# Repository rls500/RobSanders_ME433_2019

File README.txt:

Rob Sanders
4/9/2019

This is my repository for ME433 2019

This is a change

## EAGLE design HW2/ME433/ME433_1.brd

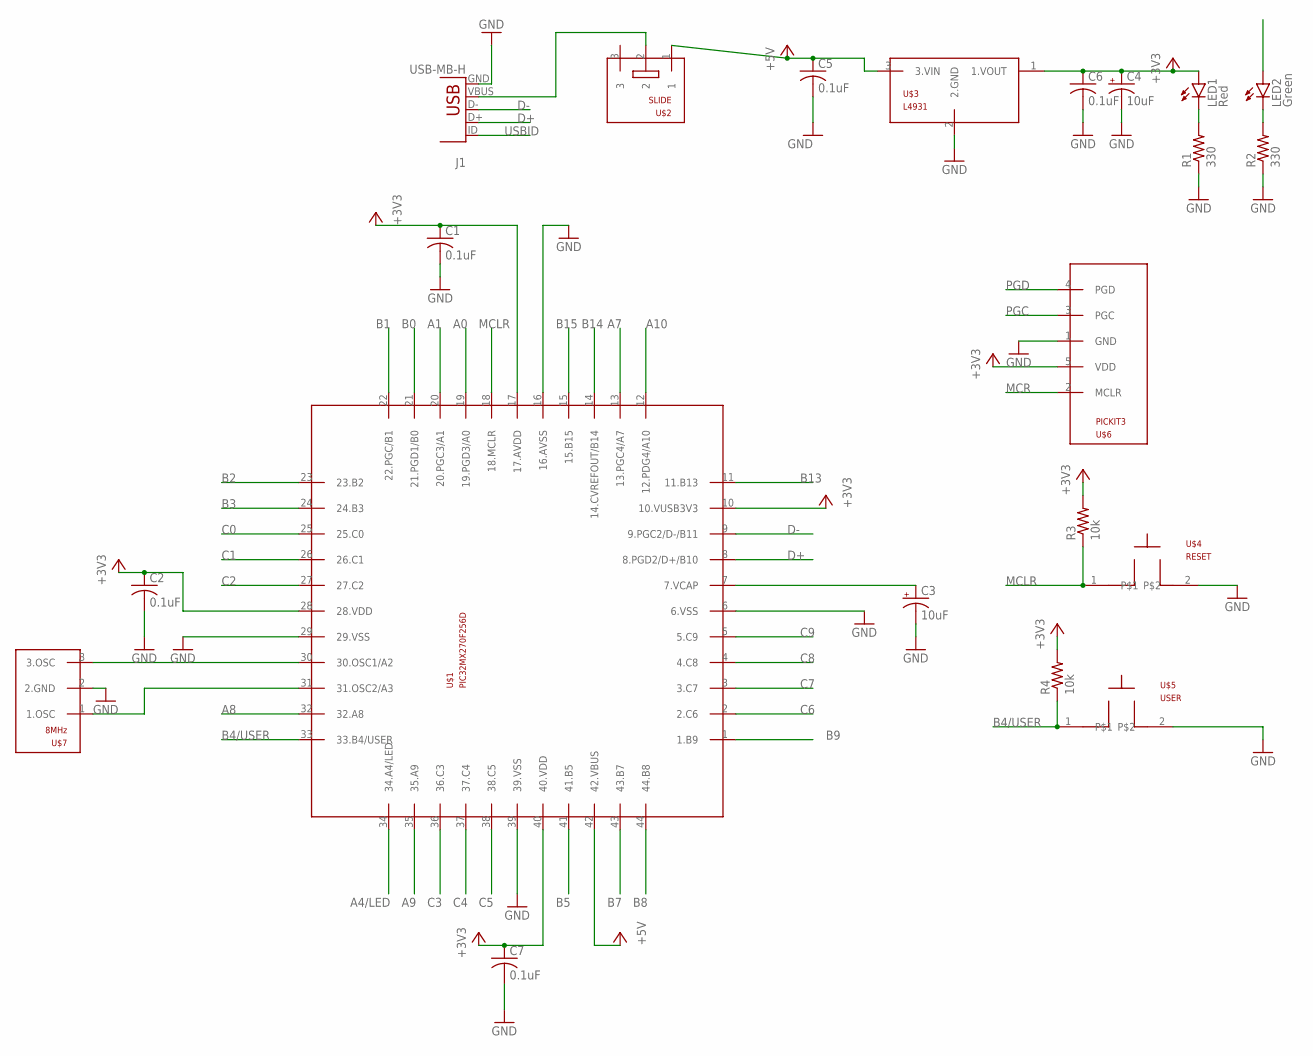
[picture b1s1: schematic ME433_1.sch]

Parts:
C1, C2, C5, C6, C7: 0.1uF; C025-025X050
C3, C4: 10uF; B45181B
J1: USB-MB-H
LED1: Red; LED3MM
LED2: Green; LED3MM
R1, R2: 330; 0207/10
R3, R4: 10k; 0207/10
U$1: PIC32MX270F256D; TQFP44
U$2: SLIDE
U$3: L4931; 1X03VREG
U$4: RESET; PB
U$5: USER; PB
U$6: PICKIT3; 1X05
U$7: 8MHz; OSC

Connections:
+3V3: C1.1, C2.1, C4.+, C6.1, C7.1, LED1.A, R3.2, R4.2, U$1.10 (10.VUSB3V3), U$1.17 (17.AVDD), U$1.28 (28.VDD), U$1.40 (40.VDD), U$3.1 (1.VOUT), U$6.5 (VDD)
+5V: C5.1, U$1.42 (42.VBUS), U$2.1, U$3.3 (3.VIN)
A0: U$1.19 (19.PGD3/A0)
A1: U$1.20 (20.PGC3/A1)
A4/LED: LED2.A, U$1.34 (34.A4/LED)
A7: U$1.13 (13.PGC4/A7)
A8: U$1.32 (32.A8)
A9: U$1.35 (35.A9)
A10: U$1.12 (12.PDG4/A10)
B0: U$1.21 (21.PGD1/B0)
B1: U$1.22 (22.PGC/B1)
B2: U$1.23 (23.B2)
B3: U$1.24 (24.B3)
B4/USER: R4.1, U$1.33 (33.B4/USER), U$5.1
B5: U$1.41 (41.B5)
B7: U$1.43 (43.B7)
B8: U$1.44 (44.B8)
B9: U$1.1 (1.B9)
B13: U$1.11 (11.B13)
B14: U$1.14 (14.CVREFOUT/B14)
B15: U$1.15 (15.B15)
C0: U$1.25 (25.C0)
C1: U$1.26 (26.C1)
C2: U$1.27 (27.C2)
C3: U$1.36 (36.C3)
C4: U$1.37 (37.C4)
C5: U$1.38 (38.C5)
C6: U$1.2 (2.C6)
C7: U$1.3 (3.C7)
C8: U$1.4 (4.C8)
C9: U$1.5 (5.C9)
D+: J1.D+, U$1.8 (8.PGD2/D+/B10)
D-: J1.D-, U$1.9 (9.PGC2/D-/B11)
GND: C1.2, C2.2, C3.-, C4.-, C5.2, C6.2, C7.2, J1.GND, R1.1, R2.1, U$1.6 (6.VSS), U$1.16 (16.AVSS), U$1.29 (29.VSS), U$1.39 (39.VSS), U$3.2 (2.GND), U$4.2, U$5.2, U$6.1 (GND), U$7.2 (2.GND)
MCLR: R3.1, U$1.18 (18.MCLR), U$4.1
MCR: U$6.2 (MCLR)
unnamed: J1.VBUS, U$2.2
unnamed: LED1.K (C), R1.2
unnamed: LED2.K (C), R2.2
unnamed: U$1.30 (30.OSC1/A2), U$7.3 (3.OSC)
unnamed: U$1.31 (31.OSC2/A3), U$7.1 (1.OSC)
unnamed: C3.+, U$1.7 (7.VCAP)
PGC: U$6.3 (PGC)
PGD: U$6.4 (PGD)
USBID: J1.ID

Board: 2 copper layers, 21 parts (1 on the bottom side), 14 nets, no tracks yet.

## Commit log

2019-04-10 :circus_tent: Added .gitattributes & .gitignore files
2019-04-10 My first commit
2019-04-10 This is a change
2019-04-15 HW1 Project
2019-04-15 HW2 Eagle Files
2019-04-15 Pragma and LED Setup
2019-04-15 Proper Timing
2019-04-15 Added Button Functionality
2019-04-17 HW 4 Complete
2019-04-17 HW Tweak
2019-04-17 Added Photos
2019-04-18 I2C Initial Setup
2019-04-18 HW4 Update
2019-04-21 HW5 i2C Functionality
2019-04-21 Finished HW5, started HW6
2019-04-21 HW 5 Diagram
2019-04-21 Updated HW5 Diagram
2019-04-22 LCD Basic Functionality
2019-04-22 Completed HW6
2019-04-29 Finished HW6
2019-05-01 Finished HW9
2019-05-08 Finished HW 8
2019-05-10 Finished HW10
2019-05-10 Renamed HW10
2019-05-13 Finished HW11
2019-05-13 Finished HW 12
2019-05-20 HW11 and 13 Pics Added
2019-06-05 Finished HW15
2019-06-05 Finished HW14
2019-06-15 HW 16
